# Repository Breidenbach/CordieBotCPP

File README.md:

# Cordiebot2
This bot was created from a brass lamp found in a resale store. CordieBot 2 is a remake of the original Arduino version which was made as a present for my granddaughter's 11th birthday.

Here is a video of the CordieBot in action...  

https://user-images.githubusercontent.com/1779744/133836883-783d6fb2-bbbe-4077-a870-86ad14fcd4a6.mp4

The original Arduino version can be found in the repository: https://github.com/Breidenbach/CordieBot .

Note that the CordieBot is a bot named after my granddaughter Cordie (duh).

The new and improved CordieBot uses a Raspberry Pi model 3 A+ with logic written in C++.

- Another version is here on github in Python, but had many mysterious memory leaks and could only run a few hours before it used up all system memory resources.  Clearly that was unacceptable, so this version was created in the hopes that I could control memory leaks better in C++ than in Python.

This version uses logic similar to the original for the light show, but now has new features:
- Uses the Cepstral voice for better speach.
- Senses the number of times the touch switch is pressed in a short time:
  -  1 touch and CordieBot says the time of day and date, possibly followed by a proclamation.
  -  2 touches and she says the current weather based on the location of the CordieBot, possibly followed by a proclamation.
  -  3 touches and she says the quote for the day from BrainyQuote.com.
  -  4 touches to repeat the previous proclamation.
  -  5 touches and she tells her version.
  -  8 touches and she tells her origin story.
  -  9 touches and she tells her internal temperature.
- Holding the button for more than 5 seconds causes a shutdown of the system, so that a reboot can occur.  CordieBot must be powered off and powered back on to reboot.
- Checks for a USB drive on start up, and when internet access is disrupted.  If the USB drive is found, checks for a new wpa_supplicant.conf file or cordiebot executable files.  If either is found, copy the file(s) using special scripts into the appropriate directory. (the executable files are only copied if the date on the files is newer than the dates on the CordieBot) Thus this version has the capability of changing the WIFI name and password without a keyboard as well as updating the software.  The USB drive is unmounted after files are copied, as it is expected that the USB drive will be removed after this process.
- This version uses multithreading to overlap the light show and speech.
- The CordieBot has an internal fan and temperature sensor, so that when the internal temperature is high the fan may help cool its logic.

## PROCLAMATIONS

After the weather and time messages, the CordieBot will randomly make a proclamation drawn from a file of messages.  There are three types of proclamations:  for a specific date, for a specific month and day of any year, and for any date.  Proclamation examples:  "Today is mom's birthday" and "I am not the droid you are looking for".  The random selection is prioritized to most often select the current day's statements, followed by those that are for any year on the current date, followed by any other statements.

The proclamation file can be updated remotely using PubNub as a secure communication channel to the CordieBot and cbot_communication on a host computer.  Messages may be added, updated, deleted, and retrieved.  Using the cordieBot_listen program on a local RaspberryPi, the messages can be checked for how they will sound when they are spoken.  Sometimes phonetic editing is required to make a message sound good.  The message text may be altered using the Speech Synthesis Markup Language (https://www.w3.org/TR/speech-synthesis11/) and then tested using a local RaspberryPi.

## DEPENDENCIES

wiringPi is used to access the Pi hardware inputs and outputs.  aoss is used to speak the phrases.

## FILES

### Library modules:
- cbotLights (.cpp and .h) provides the ramping and color change routines for the tri-color LEDs.
- cbotButton (.cpp and .h) debounces and counts presses of the touch switch.
- GPIOtoWiringpi.h maps RaspberryPi GPIO numbers to Wiring Pi numbers.
- messages (.cpp and .h) handles many functions relating to loading, updating, and storing the proclamation file.
- wiringPiMCP3002 (.cpp and .h) connects to the MCP3002 chip over SPI to read temperature values from the TMP36 sensor.
- wiringPiTLC59711 (.cpp and .h) sends data to the adafruit TLC59711 LED PWM board.

### The CordieBot application:
  - cordiebot: the main script
  - CordieBot update scripts, executed when a USB drive is sensed:
    - cordiebot_ctl.sh: copies cordiebot files from a USB drive to the current directory if the files on the USB are newer, always copiies the wpa_supplicant.conf file to /etc/wpa_supplicant
  - cordiebot_listen:  uses PubNub to communicate with the html app on home computer 
  - cordiebot_speak:  auxiliary program to receive the message from the html file and speak it.  This provides the abiity to listen to the messages prior to updating the proclamation file.  
### Scripts to remotely update the proclamation file:
  - cbot_communication.html:  communicates from a host computer to the CordieBot to maintain the file of proclamations spoken after the time is spoken.
  - Cbot_style.css:  style definitions used by cbot_communication.html
### Support files:
  - createproclamationfile.py:  Used to create an initial list of statements for the CordieBot to recite.
  - keys.js:  container for the CordieBot PubNub keyes used for communication to the CordieBot.  This file is used in all the files used in the PubNub communications - the host computer HTML file and CordieBot's listen program.
  - cordiebot_ctl.service.txt, cordiebot.service.txt, and cordiebot_listen.service.txt: These files, with the .txt extension removed, should be place in the /etc/systemd/system/ directory to start the CordieBot applications when the system is booted.

## DIRECTORY STRUCTURE

Make files and execution defaults are dependent on the file structure below.  Note that after building the application files, the executables must be moved to /home/[user]/CordiBot2 to be used automatically on boot.

/home/[user]/CordieBot2/ (Executables and scripts for running CordieBot)

/home/[user]/CordieBot2logs/  (Directory for logs when auto running at boot.  This directory must have write permissions for all.)

/home/[user]/ccpCordie/ (files for building CordieBot)
  - cbot/ (cordiebot main source files)
  - lib/ (specific libraries created for cordiebot features)
  - c-core/ (PubNub files)

## BOOT STARTUP

To start CordieBot on reboot, move the cordiebot_ctl.service.txt, cordiebot.service.txt, and cordiebot_listen.service.txt files to /etc/systemd/system/ with the .txt extension removed.  Then execute the following commands:

  - sudo systemctl disable cordiebot_ctl
  - sudo systemctl disable cordiebot
  - sudo systemctl disable cordiebot_listen
  - sudo systemctl daemon-reload
  - sudo systemctl enable cordiebot_ctl
  - sudo systemctl enable cordiebot
  - sudo systemctl enable cordiebot_listen

## PRINTED CIRCUIT BOARD

To simplify connecting to external devices and provide some interface logic, a small PCB as been developed in the format similar to the RaspberryPi HAT.  The major diference is that this board does not have the ROM to identify it to the RaspberryPi.  The board was developed using KiCad, and files for the board are included in this repository in the PCB directory.

## HARDWARE

As mentioned above, the computer for the CordieBot is a RaspberryPi model 3A+.  Additional logic includes:
-  TMP36GT9Z temperature sensor
-  MCP3002 analog to digital converter (for reading the temperature sensor)
-  PAM8302A audio amplifier
-  AT42QT1010 adafruit momentary touch sensor
-  TLC59711 adafruit 12 channel 16 bit PWM LED driver
-  Sunon GM0501PFB3-8 fan
-  HEP170 diode and 2N2222 transistor for the fan driver
-  Miscellaneos resistors, capacitors, wiring.

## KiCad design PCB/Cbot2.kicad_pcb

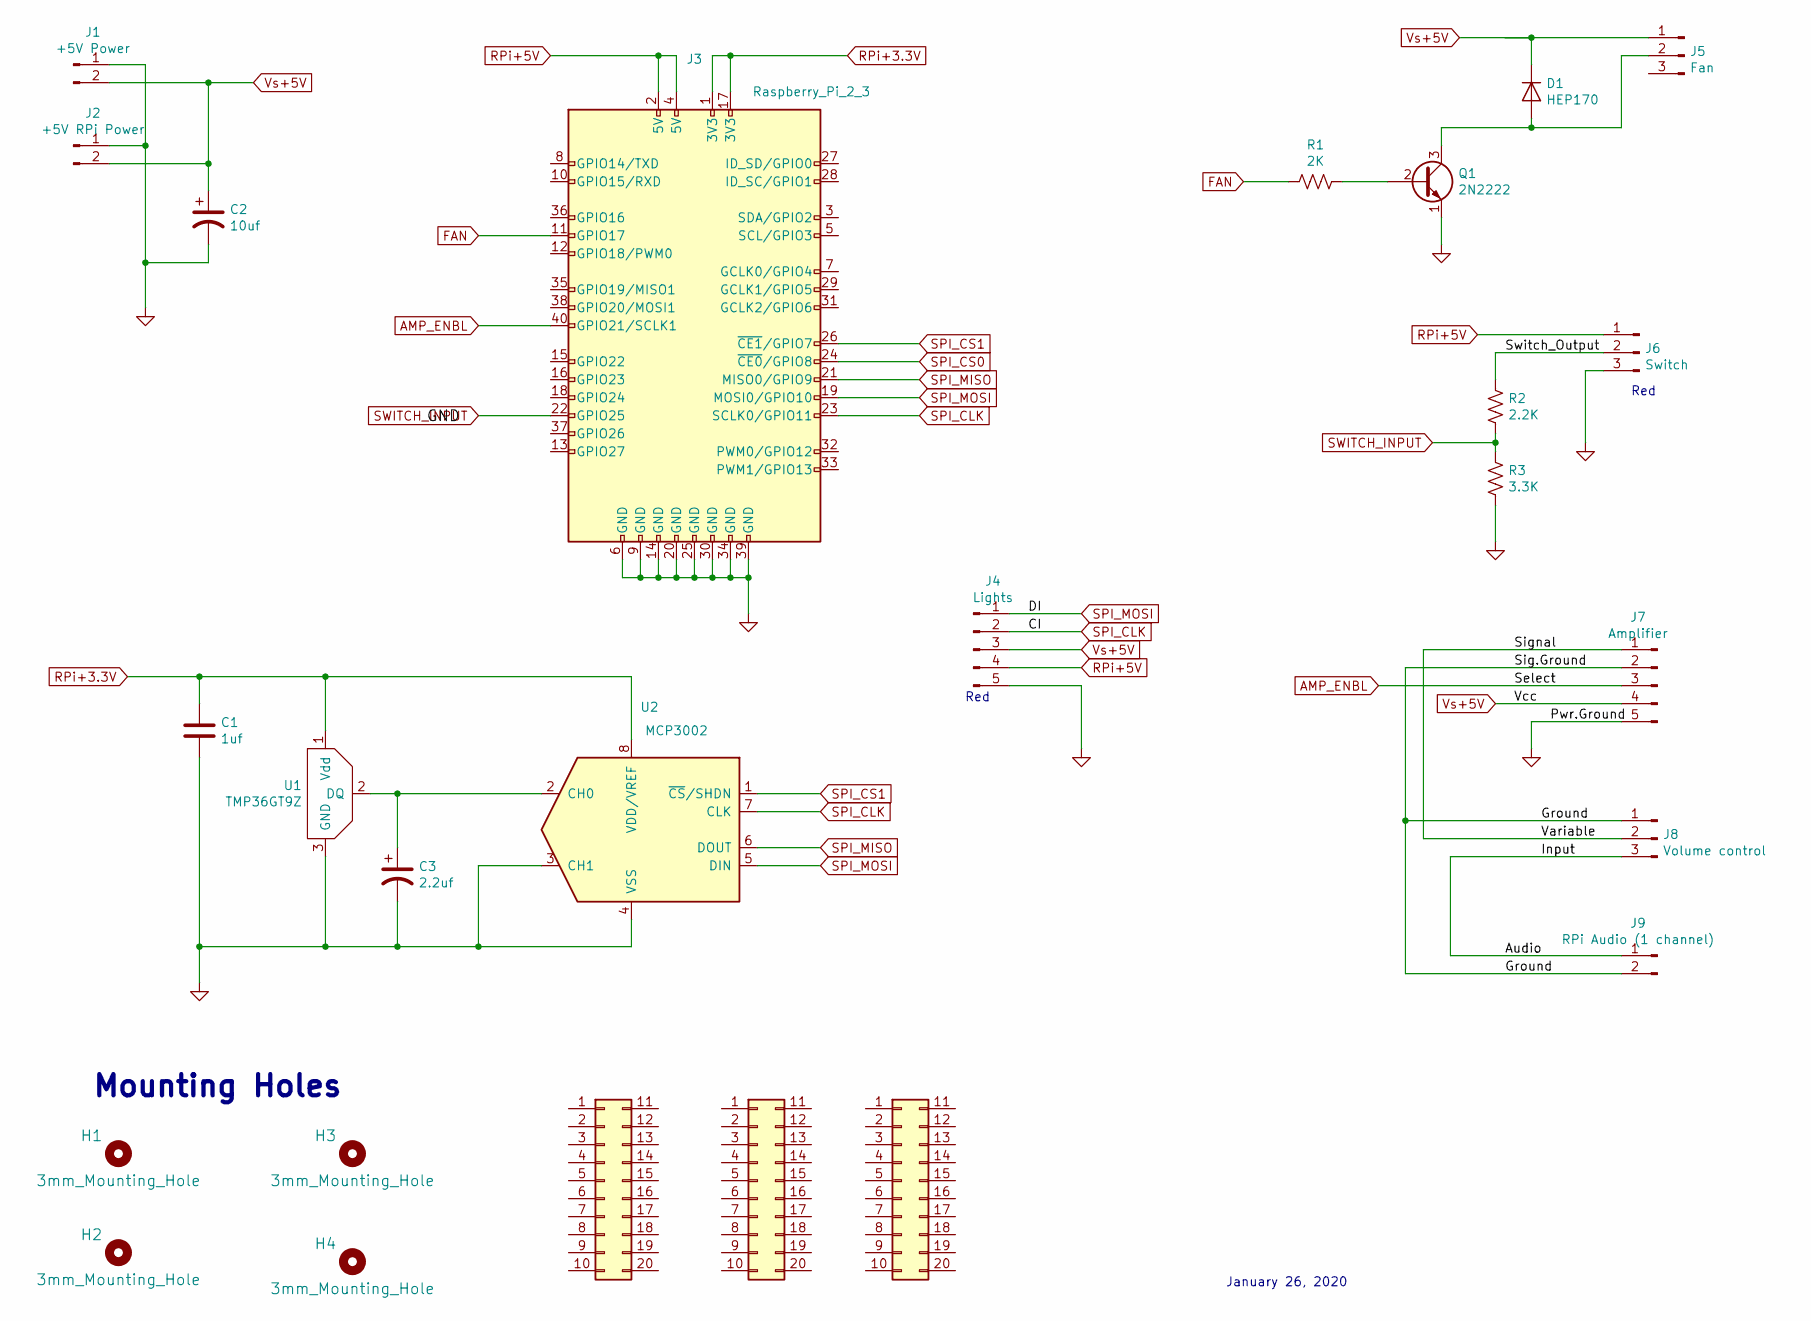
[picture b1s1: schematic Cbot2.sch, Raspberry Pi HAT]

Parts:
C1: 1uf; C_Disc_D3.0mm_W1.6mm_P2.50mm
C2: 10uf; CP_Radial_Tantal_D5.0mm_P2.50mm
C3: 2.2uf; CP_Radial_Tantal_D5.5mm_P2.50mm
D1: HEP170; D_DO-35_SOD27_P7.62mm_Horizontal
H1, H2, H3, H4: 3mm_Mounting_Hole; NPTH_3mm_ID
J1: +5V Power; PinSocket_1x02_P2.54mm_Vertical
J2: +5V RPi Power; PinSocket_1x02_P2.54mm_Vertical
J3: Raspberry_Pi_2_3; PinSocket_2x20_P2.54mm_Vertical
J4: Lights; PinSocket_1x05_P2.54mm_Vertical
J5: Fan; PinSocket_1x03_P2.54mm_Vertical
J6: Switch; PinSocket_1x03_P2.54mm_Vertical
J7: Amplifier; PinSocket_1x05_P2.54mm_Vertical
J8: Volume control; PinSocket_1x03_P2.54mm_Vertical
J9: RPi Audio (1 channel); PinSocket_1x02_P2.54mm_Vertical
J10, J11, J12: Pads; PinSocket_2x10_P2.54mm_Vertical
Q1: 2N2222; TO-92_HandSolder
R1: 2K; R_Axial_DIN0204_L3.6mm_D1.6mm_P7.62mm_Horizontal
R2: 2.2K; R_Axial_DIN0204_L3.6mm_D1.6mm_P7.62mm_Horizontal
R3: 3.3K; R_Axial_DIN0204_L3.6mm_D1.6mm_P7.62mm_Horizontal
U1: TMP36GT9Z; TO-92L_HandSolder
U2: MCP3002; DIP-8_W7.62mm

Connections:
/Audio: J8.3, J9.1
/Ground: J7.2, J8.1, J9.2
/Signal: J7.1, J8.2
/Switch_Output: J6.2, R2.1
AMP_ENBL: J3.40 (GPIO21/SCLK1), J7.3
FAN: J3.11 (GPIO17), R1.2
GND: C1.2, C2.2, C3.2, J1.1, J2.1, J3.6 (GND), J3.9 (GND), J3.14 (GND), J3.20 (GND), J3.25 (GND), J3.30 (GND), J3.34 (GND), J3.39 (GND), J4.5, J6.3, J7.5, Q1.1 (E), R3.2, U1.3 (GND), U2.3 (CH1), U2.4 (VSS)
unnamed: C3.1, U1.2 (DQ), U2.2 (CH0)
unnamed: D1.2 (A), J5.2, Q1.3 (C)
unnamed: Q1.2 (B), R1.1
RPi+3.3V: C1.1, J3.1 (3V3), J3.17 (3V3), U1.1 (Vdd), U2.8 (VDD/VREF)
RPi+5V: J3.2 (5V), J3.4 (5V), J4.4, J6.1
SPI_CLK: J3.23 (SCLK0/GPIO11), J4.2, U2.7 (CLK)
SPI_CS0: J3.24 (~CE0~/GPIO8)
SPI_CS1: J3.26 (~CE1~/GPIO7), U2.1 (~CS~/SHDN)
SPI_MISO: J3.21 (MISO0/GPIO9), U2.6 (DOUT)
SPI_MOSI: J3.19 (MOSI0/GPIO10), J4.1, U2.5 (DIN)
SWITCH_INPUT: J3.22 (GPIO25), R2.2, R3.1
Vs+5V: C2.1, D1.1 (K), J1.2, J2.2, J4.3, J5.1, J7.4

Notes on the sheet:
Red
Mounting Holes
January 26, 2020

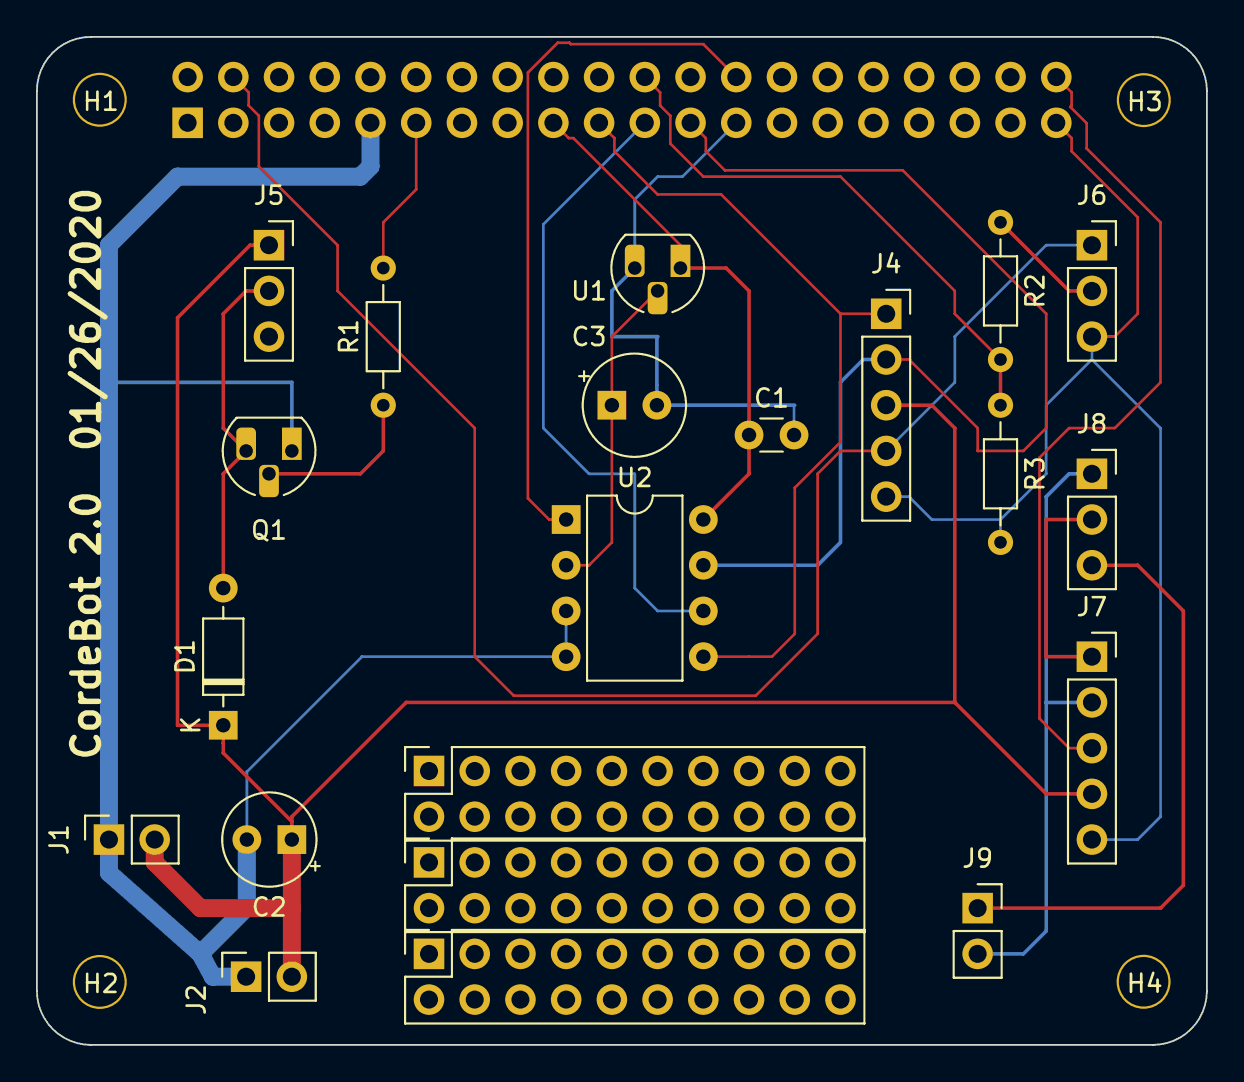
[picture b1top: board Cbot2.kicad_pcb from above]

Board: 4 copper layers, 65.0 x 56.0 mm, 26 parts (1 on the bottom side), 18 nets.

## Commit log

2019-09-12 Create LICENSE
2019-09-12 Add wiringPi connectors
    Add class .h and .c files for connecting to the MCP3002 and the adafruit TLC59711 hardware.
2019-09-17 Remove warning message
    Delete "command;" from constructor.
2019-10-04 Add proclamation maintenance files
    pubnublisten.cpp -> cordiebot_listen
    subscribe_publish_callback.cpp -> cordiebot_pubnubpipe
    cbot.mk makes these two executables.
2019-10-04 Updates regarding proclamation file programs
    Documenting the listen functions, and names of the two new c++ programs.
    Unify use of CordieBot for the name of the project.
2019-10-17 Move files to lib directory
    Move wiringPi .hpp and .cpp files to lib directory.
2019-10-17 Add messages files
    messages.cpp and .h provide routines to read and write the proclamation file.
    msgtest.cpp uses these routines to test functionality and create an initial proclamation file.
2019-11-19 Changes for add message to file
    Updates in communications and processing to handle a request to add an entry to the message file.
2019-11-20 remove obsolete version of file.
2019-11-20 lib updates for erase entry
2019-11-20 Add subnubprocess.cpp
    Without keys, plus demo key file.
    Now can Add, Delete, Retrieve an entry.
2019-11-21 cbot_communication fix box check
    When retrieving record, set correct date selection box.
2019-11-23 Finish CordieBot communication
    Add final functions to communications:
    Resequence
    Retrieve all
    Retrieve by date
2019-11-26 Clean up updates
    Revise position of some fields in messages, clean up the make file, remove obsolete files.
2019-11-26 Create wiringPiPinouts.h
    map from GPIO definitions to wiringPi pin numbers.
2019-12-01 Add touch button class
    Counts # of times touching a button
2019-12-02 Update cbot.mk
    Updates to compile cordiebot
    Some cleanup
    Use ../lib .cpp files and .o file
    Remove -g since not using debugger.
2019-12-02 Updates to make and .h files
    Use .h to trigger compiles
    Update .h to use just once
2019-12-02 Rename pubnubprocess.cpp to cordiebot_listen.cpp
2019-12-02 Add cordiebot_speak.cpp
2019-12-02 Update cbot.mk for cordiebot_speak
    Include compile of cordiebot_speak
    Change to use renamed pubnubprocess.cpp file as cordiebot_listen.cpp
2019-12-07 Add light class
    cbotLights provides LED functionality, including ramping a pair of lights up and down.
2019-12-12 Add methods to messages class
    Add methods to be used in the CordieBot app for retrieving different types of methods.
2019-12-13 Update cordiebot_speak.cpp
    Output number of characters when outputting the description. This helps in calculating the number of seconds per character to speak a statement.
2019-12-20 PCB design upload
    All files used by KiCad to create the December version of the PCB board connecting CordieBot to the various devices.
2019-12-23 Add Fan to CordieBot
    Add fan functions to CordieBot
2020-01-10 Single quote update
    Make chages so that json strings in the PubNub communication use the double quote standard, allowing single quotes to be used in swift speech interpretation.
2020-01-10 Reload messages & minor fixes
    Reload messages when the message file has changed plus a couple of minor changes.
2020-01-11 messages update
    Harden messages so it will not fail (often causing a segmentation fault) when trying to reference a value when the index has not been set.
2020-01-12 Move main cbot files to subdirectory
    This matches the make files
2020-01-14 Update cordiebot.cpp
    Use one day special message if present on first request for time.
2020-01-14 Update cordiebot_listen.cpp
    Insure action is initialized before using.
2020-01-19 USB Shell Scripts
    scripts to copy files when found on USB stick
2020-01-19 Update GPIOtoWiringPi.h
    Add missing GPIO definitions.
2020-01-26 Update cp_cordiebot.sh
    Remove copy of self to system.
    Add unlink commands so that files may be copied to system.
    Eject USB when done.
2020-01-26 Update countButton.cpp
    Improve gap detection
2020-01-26 Update wiringPiTLC59711.cpp
    Correct color LED pins
2020-01-26 Update cordiebot_listen.cpp
    Comment out #define DEBUG
    Check for Internet before trying to Publish/Subscribe.
    Align code.
    Preset action to avoid using uninitialized variable.
    Add several diagnostic messages (if DEBUG is defined)
2020-01-26 Update cordiebot.cpp
    Add includes needed to access the USB stick.
    Change FAN pin from 24 to 17
    Add diagnostic messages for issues concatenating strings
    Change string concatenation is some places to string.append()
    On startup wait for internet before announcing it isn't present.
    Revise checkFan to update a variable instead of returning a new average.
2020-01-26 Update cbot.mk
    Add GPIOtoWiringPi.h to requirements
    Add additional debut flag for finding memory leaks.
2020-01-27 PCB update
    Move signal from Raspberry Pi pin 12 to pin 11.
2020-02-03 Update cordiebot.cpp
    Change restart on long button press to simple shutdown. Rebooting will require a power off & on.
2020-02-05 Update cp_cordiebot.sh
    Add additiional files that may be copied if present:
    cp_cordiebot.sh
    cp_wpa_conf.sh
    keys.js
2020-02-07 PCB Updates
    Annotate connectors and RED markings.
2020-02-18 Update cordiebot.cpp
    Change light show to be a bit slower and intensify colors.
    Eliminate unused variable warning.
    Make "look for USB" a button option instead of start-up.
2020-02-20 Update cordiebot.cpp
    Change color delay and ramp values for head and brain lamps, to get more intense colors.
    Adjust base times and multipliers to reflect new color times and ramps.
    Reformat some lines so they could print inside normal margins.
    Add message when update files is selected (option 6) but no USB stick or files are present.
    Remove warnings about res not being used.
    Remove unused signal handler routine.
2020-03-31 Add Construction article
    Narrative of how the CordieBot is built, formatted for Microsoft Publisher. A pdf file is included for printing/reading.
2020-03-31 Create Cordie Bot story.docx
    The origin of the CordieBot
2020-06-23 Improve WIFI connectivity
    In Cordiebot, increase number of tries for WIFI before capitulating.
    Update wpa_supplicant.conf to include id of WIFI
2021-05-27 Add Boot service files
    Service files to be added to /etc/systemd/system/ so that the cordiebot and cordiebot_listen apps will start at boot.
2021-05-27 Update README.md
    Add note about the .service files to start the application at boot.
2021-06-20 Update README.md
    Include directory structure and information on where some files should be placed so that CordieBot will start on system boot.
2021-09-17 Minor changes
    update version and number of internet access attempts before giving up.
2021-09-17 Add application service.txt files
    Add files which are used start cordiebot and cordiebot_listen at system boot.
2021-09-17 Revise non-working communication
    Possibly some update of PubNub made the logic stop working, so this version moves the publish logic to a more logical spot, which corrected that problem.
2021-09-17 Add note about log directory.
    Update directory structure section due to changes in cordiebot.service and cordiebot_listen.service .
2021-09-17 Add video of CordieBot in action
2021-09-17 Spelling correction
2021-09-17 Comment out #define DEBUG
    Turn off debug message creation
2021-09-20 Update messages.cpp
    Correct problem reading past end of messages for date.
2021-09-20 Update cordiebot_listen.cpp
    When starting, delay PubNub until internet access is confirmed.
    Add logging for each entry received.
2021-09-23 Clean interaction between html and listen
    Implement a new signal between the html communication file and cordiebot_listen so that fields will be blanked out when data is not returned. Affects the get by number, get by date, and get all reque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
    Also add the uuid field to the PubNub setup and a timestamp the the console messages.
2021-09-24 service file updates
    cordiebot_listen: correct adding exec
    cordiebot: put in nice priority
2021-09-24 Update cordiebot.cpp
    Speak "Hi" at startup
    Start speak commands with higher priority
2021-09-30 Update cordiebot.service.txt
    Set CordieBot nice to a higher value than Swift so that audio will have priority over CordieBot itself.
2021-11-27 Update cbot_communication.html
    Corrections to set button when retrieving all
    Put in semicolons for consistency
2021-11-27 Update cordiebot.cpp
    change geolocation web site name
    change nice on aoss to -8 from -5
    fix comment in tellDailyQuote
    change version to 2.2 and update date
    change touch button gap to 0.8 from 0.6
2021-12-24 Update README.md
    Mention the existence and use of the cordiebot_speak program.
2021-12-24 Update cordiebot_speak.cpp
    Allow time to test for wifi connection after starting, allowing the program to execute successfully when started at boot.
    Bypass error message when an empty message is received.
    Use #ifdef DEBUG to avoid outputing messages needed only for diagnostics.
2021-12-25 Update cordiebot.cpp
    Change aoss swift nice to -15, higher priority to smooth out speaking.
2022-02-27 Initialization routine changes
    Update copy functions in cordiebot.cpp
    Reorganize service routines so that cordiebot_ctl.service executes first, allowing cordiebot.service and cordiebot_listen.service to then execute.
    Replace cp_cordiebot.sh and cp_wpa_conf.sh with cordiebot_ctl.sh.
    Change copy routines in cordiebot_ctl.sh to copy executables only if the USB date is new than the CordieBot date.
    Mount the USB memory in cordiebot_ctl.sh.
2022-02-27 Update README.md
    Comment on changes due to revising the systemd service files and the cordiebot_ctl.sh bash script.
2024-04-13 Update LICENSE
